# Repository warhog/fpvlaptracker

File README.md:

# fpvlaptracker

master: 

dev: 

licensed under [MIT](LICENSE.md)

open source diy fpv vtx lap tracking system

## features
- uses your analog vtx to do the lap detection
- 48 channels supported
- standalone (app) or connected mode (web frontend) available for single practicing or fun with friends
- connected mode supports up to 8 tracker units and comfortable access using web ui
- 2ms accuracy (tested with 4 parallel nodes)

## how does it work?
the tracker unit measures the video signal strength (rssi) of the selected video channel to detect laps using peak detection. it has a stand alone mode for single participants or a connected mode supporting multiple participants and a web ui. in standalone mode the tracker unit is controlled using bluetooth and a mobile app for configuration and single user race (e.g. practicing). the connected mode is used with any hardware that can run the java software backend.

### app
the tracker unit is accessed using bluetooth and a mobile application (older version was creating an wifi ap and serving a webpage but that was horrible slow). using the app one can configure the unit or run single user races (e.g. practicing).

the application is available in the play store (only android right now, [play store](https://play.google.com/store/apps/details?id=de.warhog.fpvlaptracker)), the source is in the app folder).

### standalone mode
the tracker can be used in standalone mode for single user races. only one tracker node and the app is needed.

### connected mode
running in the connected mode the tracker connects to a host software using wifi. races and particpants can be organized inside the host software. the host software includes a webserver that serves a web ui for watching / controlling races. one to multiple (max. 8) tracker nodes and server with wifi (e.g. raspi) required.

## tested devices
* immersion rc vtx
* blade inductrix fpv
* boscam ts5828
* eachine et526
* tbs unify pro hv
* betafpv 75s

## setup
[setup instructions](docs/setup.md)
    
## which hardware and software is used?
the hardware consists of a esp32 board with a boscam rx5808 receiver module connected. the esp32 runs the tracker firmware (written using Arduino software platform).
the backend of the race software for connected mode was written in java using spring boot 2. the frontend was developed using angular 8. the race software can be run on almost every platform that supports java se.
due to the low price, simplicity and size a raspberry pi (>= 2) powered by a power bank is the optimum solution for mobile usage.

# repository information
this repository contains everything needed to build your own tracker(s).

* app: the mobile app
* firmware: firmware for a single node
* hardware: hardware for a single node
* web: the java backend and web frontend for multiple node races

## sound files used
_lap:_ [freesound](https://www.freesound.org/people/StaneStane/sounds/73560/)

texts: [fromtexttospeech.com](http://www.fromtexttospeech.com/)

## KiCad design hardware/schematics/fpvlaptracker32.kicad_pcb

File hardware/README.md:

# fpvlaptracker

this is the currently used hardware platform based on esp32 and rx5808.

for firmware building and flashing [read this](../docs/firmware.md)

## pictures

## schematics
the schematics and pcb are drawn using KiCAD5 (see schematics folder).

[pdf schematics](https://raw.githubusercontent.com/warhog/fpvlaptracker/master/hardware/schematics/schematic.pdf)

## bom (bill of material)

most of the pcb parts are found in the [bom csv file](https://github.com/warhog/fpvlaptracker/blob/master/hardware/fpvlaptracker32-bom.csv).

some additional parts are needed optionally:
* heatsink with 20x20 mm and heatsink glue for the rx5808
* 5v power supply board if you want to power from a LiPo, ..., i used the [pololu D24V10F5](https://www.pololu.com/product/2831) for this.

## housing

there is a 3d printable housing availbe in the housing folder. printing in pla with 0.2 mm layer height is enough. no supports needed.

## gerber files

if you want to make your own pcb you can use the gerber files in the gerber folder. i've used itead and elecrow and both were fine (itead is a bit cheaper, elecrow was quicker).

## rx5808 5,8 GHz receiver mod
the rx5808 receiver needs to be modified to support the SPI protocol.
an excellent description by shea ivey can be found [here](https://github.com/sheaivey/rx5808-pro-diversity/blob/master/docs/rx5808-spi-mod.md).

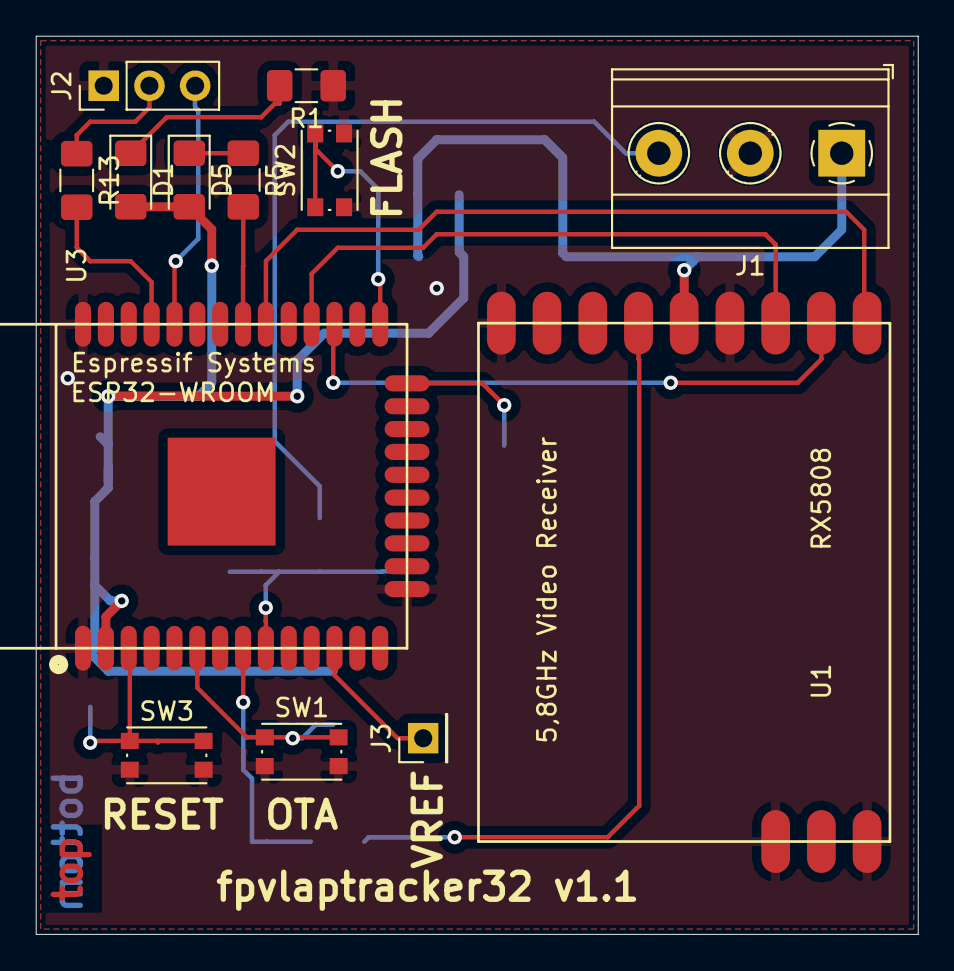
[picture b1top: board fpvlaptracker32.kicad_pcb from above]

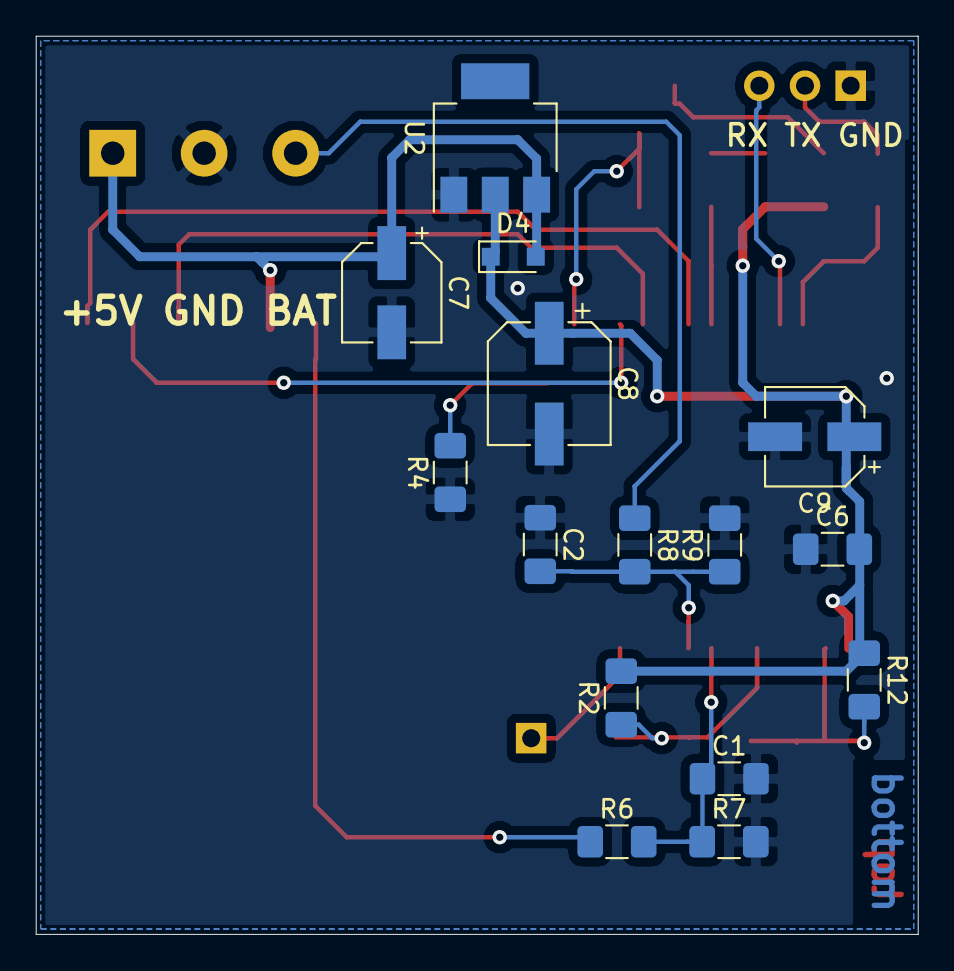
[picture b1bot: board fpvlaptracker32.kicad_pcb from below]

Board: 2 copper layers, 49.0 x 49.9 mm, 28 parts (15 on the bottom side), 21 nets.

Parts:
C1, C2, C6: 100nF; C_1206_3216Metric_Pad1.42x1.75mm_HandSolder
C7, C9: 10µF; CP_Elec_5x4.4
C8: 100µF; CP_Elec_6.3x5.4
D1, D5: LED; LED_1206_3216Metric_Pad1.42x1.75mm_HandSolder
D4: DIODE; D_SOD-323_HandSoldering
J1: Screw_Terminal_01x03; TerminalBlock_Phoenix_MKDS-1,5-3-5.08_1x03_P5.08mm_Horizont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
J2: Serial; PinHeader_1x03_P2.54mm_Vertical
J3: Conn_01x01_Female; PinHeader_1x01_P2.54mm_Vertical
R1, R9: 1k; R_1206_3216Metric_Pad1.42x1.75mm_HandSolder
R2, R6, R7, R8, R12: 10k; R_1206_3216Metric_Pad1.42x1.75mm_HandSolder
R4: 5k; R_1206_3216Metric_Pad1.42x1.75mm_HandSolder
R5: 100; R_1206_3216Metric_Pad1.42x1.75mm_HandSolder
R13: 470; R_1206_3216Metric_Pad1.42x1.75mm_HandSolder
SW1: Webupdate; SW_SPST_KMR2
SW2: Prog; SW_SPST_KMR2
SW3: Reset; SW_SPST_KMR2
U1: RX5808
U2: LM1117-3.3; SOT-223
U3: ESP-32_WROOM32; ESP32-WROOM

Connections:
+3V3: C6.2, C8.1, C9.1, D1.2, D4.1, D5.2, R2.2, R12.1, U2.2, U3.2
+5V: C7.1, D4.2, J1.1, U1.8, U2.3
/ADC_REF: J3.1, U3.12
/ANALOG_BAT: C2.2, R8.2, R9.1, U3.9
/ANALOG_RSSI: C1.1, R6.2, R7.1, U3.8
/BAT: J1.3, R8.1
/EN: R12.2, SW3.1, U3.3
/IO0: SW2.1, U3.25
/LED: R5.2, U3.31
/RSSI: R6.1, U1.9
/RXD: J2.3, U3.34
/SPI_CLK: U1.6, U3.28
/SPI_CS: U1.5, U3.27
/SPI_DATA: U1.4, U3.30
/TXD: J2.2, R13.1
/WEB_UPDATE: R2.1, SW1.1, U3.6
GND: C1.2, C2.1, C6.1, C7.2, C8.2, C9.2, J1.2, J2.1, R1.1, R4.1, R7.2, R9.2, SW1.2, SW2.2, SW3.2, U1.1, U1.3, U1.7, U1.12, U2.1, U3.1, U3.15, U3.38
unnamed: D1.1, R1.2
unnamed: D5.1, R5.1
unnamed: R4.2, U3.24
unnamed: R13.2, U3.35

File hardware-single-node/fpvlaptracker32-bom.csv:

Id,Designator,Package,Quantity,Designation,Supplier and ref
1,SW2,SW_SPST_KMR2,1,Prog,https://www.reichelt.de/smd-kurzhubtaster-4-2-x-2-8-mm-hoehe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
2,SW3,SW_SPST_KMR2,1,Reset,https://www.reichelt.de/smd-kurzhubtaster-4-2-x-2-8-mm-hoehe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
3,SW1,SW_SPST_KMR2,1,Webupdate,https://www.reichelt.de/smd-kurzhubtaster-4-2-x-2-8-mm-hoehe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
4,J1,"TerminalBlock_Phoenix_MKDS-1,5-3-5.08_1x03_P5.08mm_Horizontal",1,Screw_Terminal_01x03,https://www.reichelt.de/loetbare-schraubklemme-3-pol-rm-5-08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
5,U2,SOT-223,1,LM1117-3.3,https://www.reichelt.de/ldo-spannungsregler-3-3-v-sot-223-lm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
6,D4,D_SOD-323_HandSoldering,1,DIODE,https://www.reichelt.de/gleichrichterdiode-75-v-0-15-a-sod-3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
7,U1,RX5808,1,RX5808,https://www.banggood.com/FPV-Wireless-Audio-Video-Receiving-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
8,"C6,C1,C2",C_1206_3216Metric_Pad1.42x1.75mm_HandSolder,3,100nF,https://www.reichelt.de/smd-kerko-1206-100-nf-25-v-10-mlcc-r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
9,"R1,R9",R_1206_3216Metric_Pad1.42x1.75mm_HandSolder,2,1k,https://www.reichelt.de/smd-widerstand-1206-1-0-kohm-250-mw-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
10,R4,R_1206_3216Metric_Pad1.42x1.75mm_HandSolder,1,5k,https://www.reichelt.de/smd-widerstand-1206-5-1-kohm-250-mw-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
11,"R6,R7,R8,R12,R2",R_1206_3216Metric_Pad1.42x1.75mm_HandSolder,5,10k,https://www.reichelt.de/smd-widerstand-1206-10-kohm-250-mw-1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
12,R13,R_1206_3216Metric_Pad1.42x1.75mm_HandSolder,1,470,https://www.reichelt.de/smd-widerstand-1206-470-ohm-250-mw-1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
13,U3,ESP32-WROOM,1,ESP-32_WROOM32,"ebay, elecrow"
14,"D1,D5",LED_1206_3216Metric_Pad1.42x1.75mm_HandSolder,2,LED,https://www.reichelt.de/led-smd-1206-gruen-350-mcd-50-kbt-kp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
,,,,,https://www.reichelt.de/led-smd-1206-rot-80-mcd-120-kbt-kp-3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
15,"C7,C9",CP_Elec_5x4.4,2,10µF,https://www.reichelt.de/smd-chip-elko-10-f-16volt-smd-elko-1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
16,C8,CP_Elec_6.3x5.4,1,100µF,https://www.reichelt.de/smd-chip-elko-100-f-16volt-smd-elko-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
17,R5,R_1206_3216Metric_Pad1.42x1.75mm_HandSolder,1,100,https://www.reichelt.de/smd-widerstand-1206-100-ohm-250-mw-1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
18,J2,PinHeader_1x03_P2.54mm_Vertical,1,Serial,https://www.reichelt.de/20pol-buchsenleiste-gerade-rm-2-54-h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
19,J3,PinHeader_1x01_P2.54mm_Vertical,1,Conn_01x01_Female,https://www.reichelt.de/20pol-buchsenleiste-gerade-rm-2-54-h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

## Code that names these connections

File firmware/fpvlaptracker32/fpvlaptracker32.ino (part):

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// pin configurations
const unsigned int PIN_SPI_SLAVE_SELECT = 16;
const unsigned int PIN_SPI_CLOCK = 17;
const unsigned int PIN_SPI_DATA = 18;
const unsigned int PIN_LED = 19;
const unsigned int PIN_ANALOG_RSSI = 32;
const unsigned int PIN_WEB_UPDATE = 34;
const unsigned int PIN_ANALOG_BATTERY = 33;

lap::Rssi rssi(PIN_ANALOG_RSSI);
ledio::LedControl led(PIN_LED);
util::Storage storage;
lap::LapDetector lapDetector(&storage, &rssi);
comm::WifiComm wifiComm(&storage);
radio::Rx5808 rx5808(PIN_SPI_CLOCK, PIN_SPI_DATA, PIN_SPI_SLAVE_SELECT, PIN_ANALOG_RSSI);
BluetoothSerial btSerial;
battery::BatteryMgr batteryMgr(PIN_ANALOG_BATTERY);
statemanagement::StateManager stateManager;
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	Serial.println(F("setting up ports"));
#endif
	rx5808.init();
	pinMode(PIN_WEB_UPDATE, INPUT_PULLUP);
	if (digitalRead(PIN_WEB_UPDATE) == LOW) {
#ifdef DEBUG
		Serial.println(F("enabling webupdate mode"));
#endif		
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
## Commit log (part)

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2017-04-23 initial code commit
2017-04-23 try to fix travis for multi language project
2017-04-23 fix gulp-sourcemaps issue again :)
2017-04-23 added missing gulp-rename to node config
2017-04-23 try to force new node version
2017-04-23 change before_install
2017-04-23 build jooq schema sources before build
2017-04-23 remove jooq generation from build task
2017-04-23 rename raceservice to racedbservice
2017-04-26 introduction of participant race service
2017-04-26 moved racestate to entities
2017-05-07 Create base_rpi
2017-05-23 many improvements in audio handling
2017-08-15 added multi language audio
2017-08-15 added hardware folder, added stl files for case
2017-08-22 improved audio service
2017-08-22 register as bluetooth unit
2017-08-25 refactoring of firmware code
2017-09-09 Rename configuration to configuration.md
2017-10-15 bump to version 0.2
2017-10-31 added channel scanner
2018-06-29 first draft of new bluetooth node firmware
2018-06-30 added serial communication to app, improved bt init on soft reset, made frequency class singleton
2018-07-10 make name changeable on bluetooth trackers
2018-07-15 use functions from timeutil
2018-08-11 added fpvlaptracker32
2018-08-11 added rssi to bluetooth lap data, added runtimedata
2018-08-23 fix buffer overrun
2018-08-23 change webupdate port
2018-08-24 improved dataexchange, small fixes
2018-08-25 better chipid
2018-08-25 improve first data message handling
2018-08-25 added cell getter to blink the number of detected cells on startup
2018-08-26 new defaults for trigger threshold and calibration offset
2018-08-27 moved firmware to separate repo
2018-09-09 bump version to 0.4
2018-09-12 updated dependencies, bumped version
2018-09-13 removed hardware files
2018-10-03 full esp32 tracker support
2018-10-03 improve and fix reboot handling
2018-10-07 fixed save of defaultvref and minlaptime
2018-10-13 added udp thread status, added favicon
2018-10-19 improve exception handling to make sure udphandler does never quit
2018-10-26 removed audio files
2018-11-08 unsubscribe lap listener as well
2018-11-28 make restservice more robust update websocketconfig to implement websocketmessagebrokerconfigurer
2018-12-19 introduction of project version
2018-12-19 add paths to fix compilation from ide
2018-12-19 added example configuration file
2018-12-19 removed old theme file from gulp
2018-12-19 adaptions for bootstrap 4
2018-12-19 reorder items, add cell voltage
2018-12-19 scroll to top after save
2018-12-19 added lowbattery and message udp packets and handling
2018-12-19 changed badge color for race badge
2018-12-19 introduce release_files
2018-12-19 checkout at the end
2018-12-22 introduce language files
2018-12-22 improve subscription handling
2018-12-22 simplify message handling
2018-12-23 fixed removal of inactive tracker nodes added timeout for RestTemplate resolved findbugs warnings
2018-12-23 fix blocking speak method
2018-12-23 make permanent switchable for danger alerts
2018-12-23 copy language files on release
2019-02-23 first test of fixed races
2019-02-23 updated bootstrap
2019-03-08 added skip calibration feature
2019-03-08 added rssi text, fixed small issues with calibration skipping
2019-03-09 lots of changes...
2019-03-09 moved some classes
2019-03-09 added race aborted text
2019-03-09 don't show invalid laps on chart
2019-03-10 added additional status and duration for pilots based on modes
2019-03-10 change race mode using buttons instead ofselect
2019-03-10 fixed duration display
2019-03-10 added no profile text
2019-03-22 added basic installer, added systemd service instead of start script
2019-03-22 improve startup
2019-03-22 inplace sed, freshen files from zip
2019-03-22 removed user
2019-03-27 fixed toplist, fixed first lap issue with round based races, small fixes
2019-05-03 updated jquery
2019-05-28 use -o instead of -f (force overwrite) in installer
2019-07-18 combined single repos back into one repo
2019-07-18 changed folder names
2019-07-19 switch to gulp-inject-version2
2019-07-19 add .gradle to ignore list
2019-07-31 update gradle versions
2019-08-15 complete refactoring of web ui and backend, adaptions on firmware for those changes
2019-08-15 fix findbugs warnings
2019-08-15 fix sed call
2019-08-15 added autofocus directive, added autofocus to login, added shutdown delay, fix missing login error message
2019-08-22 added queue for udp packets for faster packet handling
2019-08-22 removed fastrssi mode
2019-08-25 fix rssi packet issue, added overlay to update, added ssid+password to data
2019-08-29 beta release of new app
2019-09-01 fix length of alerts on mobile devices
2019-09-01 fix fullscreen in device view, fix issue when no tracker selected
2019-09-16 reformat styles, added bold
2019-09-18 streamline versions to be 3.0 for app, web and firmware
2019-09-26 move build banner to header
2019-09-27 fix tree test
2019-09-27 fix tag detection in build scripts
2019-09-27 try to fix deployment
2019-09-27 add library versions
2019-09-27 fix missing application properties files due to gitignore error
2019-09-27 add chipid to mdns node name
2019-09-27 add title to node ui
2019-09-27 fix reboot from ui
2019-09-27 bump version to 3.1.0
2019-09-28 added rssi to node web ui improved version commit on node web ui changed web ui calls to node to /api added node factory defaults for webui fix nodesetup webui redirector change log level to info all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
2019-09-30 update node data on nodes overview
2019-09-30 fix wording for node count beeing pronounced as third instead of three.
2019-09-30 add node availability check
2019-10-01 add wifi settings to node ui, small improvements on webui
2019-10-01 update documentation
2019-10-01 improve loading on nodes screen, sync nodes access, add firmware zip deployment
2019-10-01 disable nodesetup on offline nodes
2019-10-02 enable debug mode
2019-12-29 Bump handlebars from 4.1.2 to 4.5.3 in /web/webpage
    Bumps [handlebars](https://github.com/wycats/handlebars.js) from 4.1.2 to 4.5.3.
    - [Release notes](https://github.com/wycats/handlebars.js/releases)
    - [Changelog](https://github.com/wycats/handlebars.js/blob/master/release-notes.md)
    - [Commits](https://github.com/wycats/handlebars.js/compare/v4.1.2...v4.5.3)
2020-03-15 Bump acorn from 5.7.3 to 5.7.4 in /web/webpage
    Bumps [acorn](https://github.com/acornjs/acorn) from 5.7.3 to 5.7.4.
    - [Release notes](https://github.com/acornjs/acorn/releases)
    - [Commits](https://github.com/acornjs/acorn/compare/5.7.3...5.7.4)
2020-04-03 Bump acorn from 6.3.0 to 6.4.1 in /app
    Bumps [acorn](https://github.com/acornjs/acorn) from 6.3.0 to 6.4.1.
    - [Release notes](https://github.com/acornjs/acorn/releases)
    - [Commits](https://github.com/acornjs/acorn/compare/6.3.0...6.4.1)
2020-04-16 Bump https-proxy-agent from 2.2.2 to 2.2.4 in /app
    Bumps [https-proxy-agent](https://github.com/TooTallNate/node-https-proxy-agent) from 2.2.2 to 2.2.4.
    - [Release notes](https://github.com/TooTallNate/node-https-proxy-agent/releases)
    - [Commits](https://github.com/TooTallNate/node-https-proxy-agent/compare/2.2.2...2.2.4)
2020-04-30 Bump jquery from 3.4.1 to 3.5.0 in /web/webpage
    Bumps [jquery](https://github.com/jquery/jquery) from 3.4.1 to 3.5.0.
    - [Release notes](https://github.com/jquery/jquery/releases)
    - [Commits](https://github.com/jquery/jquery/compare/3.4.1...3.5.0)
2020-06-07 Bump websocket-extensions from 0.1.3 to 0.1.4 in /web/webpage
    Bumps [websocket-extensions](https://github.com/faye/websocket-extensions-node) from 0.1.3 to 0.1.4.
    - [Release notes](https://github.com/faye/websocket-extensions-node/releases)
    - [Changelog](https://github.com/faye/websocket-extensions-node/blob/master/CHANGELOG.md)
    - [Commits](https://github.com/faye/websocket-extensions-node/compare/0.1.3...0.1.4)
2020-06-18 Bump angular from 1.7.9 to 1.8.0 in /web
    Bumps [angular](https://github.com/angular/angular.js) from 1.7.9 to 1.8.0.
    - [Release notes](https://github.com/angular/angular.js/releases)
    - [Changelog](https://github.com/angular/angular.js/blob/master/CHANGELOG.md)
    - [Commits](https://github.com/angular/angular.js/compare/v1.7.9...v1.8.0)
2020-07-17 Bump lodash from 4.17.14 to 4.17.19 in /web
    Bumps [lodash](https://github.com/lodash/lodash) from 4.17.14 to 4.17.19.
    - [Release notes](https://github.com/lodash/lodash/releases)
    - [Commits](https://github.com/lodash/lodash/compare/4.17.14...4.17.19)
2020-07-18 Bump lodash from 4.17.15 to 4.17.19 in /app
    Bumps [lodash](https://github.com/lodash/lodash) from 4.17.15 to 4.17.19.
    - [Release notes](https://github.com/lodash/lodash/releases)
    - [Commits](https://github.com/lodash/lodash/compare/4.17.15...4.17.19)
2020-07-31 Bump elliptic from 6.5.0 to 6.5.3 in /app
    Bumps [elliptic](https://github.com/indutny/elliptic) from 6.5.0 to 6.5.3.
    - [Release notes](https://github.com/indutny/elliptic/releases)
    - [Commits](https://github.com/indutny/elliptic/compare/v6.5.0...v6.5.3)
2020-09-10 Bump http-proxy from 1.17.0 to 1.18.1 in /app
    Bumps [http-proxy](https://github.com/http-party/node-http-proxy) from 1.17.0 to 1.18.1.
    - [Release notes](https://github.com/http-party/node-http-proxy/releases)
    - [Changelog](https://github.com/http-party/node-http-proxy/blob/master/CHANGELOG.md)
    - [Commits](https://github.com/http-party/node-http-proxy/compare/1.17.0...1.18.1)
2021-03-09 Bump elliptic from 6.5.0 to 6.5.4 in /app
    Bumps [elliptic](https://github.com/indutny/elliptic) from 6.5.0 to 6.5.4.
    - [Release notes](https://github.com/indutny/elliptic/releases)
    - [Commits](https://github.com/indutny/elliptic/compare/v6.5.0...v6.5.4)
2021-03-30 Bump y18n from 4.0.0 to 4.0.1 in /app
    Bumps [y18n](https://github.com/yargs/y18n) from 4.0.0 to 4.0.1.
    - [Release notes](https://github.com/yargs/y18n/releases)
    - [Changelog](https://github.com/yargs/y18n/blob/master/CHANGELOG.md)
    - [Commits](https://github.com/yargs/y18n/commits)
2021-04-30 Bump ssri from 6.0.1 to 6.0.2 in /app
    Bumps [ssri](https://github.com/npm/ssri) from 6.0.1 to 6.0.2.
    - [Release notes](https://github.com/npm/ssri/releases)
    - [Changelog](https://github.com/npm/ssri/blob/v6.0.2/CHANGELOG.md)
    - [Commits](https://github.com/npm/ssri/compare/v6.0.1...v6.0.2)
2021-05-08 Bump handlebars from 4.5.3 to 4.7.7 in /web/webpage
    Bumps [handlebars](https://github.com/wycats/handlebars.js) from 4.5.3 to 4.7.7.
    - [Release notes](https://github.com/wycats/handlebars.js/releases)
    - [Changelog](https://github.com/handlebars-lang/handlebars.js/blob/master/release-notes.md)
    - [Commits](https://github.com/wycats/handlebars.js/compare/v4.5.3...v4.7.7)
2021-05-08 Bump url-parse from 1.4.4 to 1.5.1 in /web
    Bumps [url-parse](https://github.com/unshiftio/url-parse) from 1.4.4 to 1.5.1.
    - [Release notes](https://github.com/unshiftio/url-parse/releases)
    - [Commits](https://github.com/unshiftio/url-parse/compare/1.4.4...1.5.1)
2021-05-08 Bump url-parse from 1.4.7 to 1.5.1 in /app
    Bumps [url-parse](https://github.com/unshiftio/url-parse) from 1.4.7 to 1.5.1.
    - [Release notes](https://github.com/unshiftio/url-parse/releases)
    - [Commits](https://github.com/unshiftio/url-parse/compare/1.4.7...1.5.1)
2021-05-10 Bump lodash from 4.17.15 to 4.17.21 in /web/webpage
    Bumps [lodash](https://github.com/lodash/lodash) from 4.17.15 to 4.17.21.
    - [Release notes](https://github.com/lodash/lodash/releases)
    - [Commits](https://github.com/lodash/lodash/compare/4.17.15...4.17.21)

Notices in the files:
firmware/fpvlaptracker32/fpvlaptracker32.ino:
The MIT License (MIT)
Copyright (c) 2017-2018 warhog
